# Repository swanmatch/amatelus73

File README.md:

# Amatelus73ビルドガイド

## 概要

m.teiさんの[セミエルゴレイアウト](https://github.com/mtei/SemiErgo_Layout)を参考に作成したシンメトリカルスタッガードキーボード。  
RGBMATRIXに標準対応しているのも特徴。

### 材料リスト

| 品目                    | 数量 | 備考 |
| :---------------------- | ---: | :--- |
| PCB                     |  1枚 |  |
| トッププレート          |  1枚 |  |
| ボトムプレート          |  1枚 |  |
| アクリル保護プレート    |  2枚 |  |
| ProMicro                |  1個 |  |
| ダイオード              | 73個 | スピーカーを使う場合74個。<br>スルーホールは使えないので注意。 |
| LED(YS-SK6812mini)      | 74個 |  |
| Kailhソケット           | 73個 |  |
| M2L4ネジ                | 18本 |  |
| M2L7六角スペーサ        |  5本 |  |
| M2L8丸スペーサ          |  4本 |  |
| タクトスイッチ          |  1個 |  |
| ゴム足                  |  4個 |  |
| 2Uスタビライザー         |  4個 |  |
| MX互換スイッチ          | 73個 |  |
| キーキャップ            | 73個 |  |
| USBケーブル             |  1本 |  |

### オプション機能

| 品目             | 数量 | 備考 |
| :--------------- | ---: | :--- |
| コンスルー       |  2本 |  |
| 圧電サウンダ     |  1個 | スピーカーオプション<br>型番: PKMCS1212E4000-R1 |
| 1kΩ抵抗         |  1個 | スピーカーオプション |
| OLED             |  1個 | ピン、ソケットも。 |

## 組み立て手順

### LED

LEDをはんだ付けします。  
小さくドットが入っているのが欠けている足に対応しています。

行ごと向きが違うので注意してください。

### ダイオード

ダイオードをはんだ付けします。  
向きに気をつけてください。  
うっすら線が書いてあるほうが左です。

先に予備ハンダとしてどちらかのパッドにハンダを盛って、
予備ハンダを溶かすようにしてダイオードの片足をはんだ付けします。  
この状態で横から見てダイオードが浮いていないことを確認してください。  
浮いてしまっている場合はダイオードをピンセットで押さえつけながら、
はんだづけした部分を再度熱すればきれいになります。

浮いていないことを確認し、反対側をはんだ付けします。

### ソケット

ソケットをはんだ付けします。

### リセットスイッチ

反対側(表、スイッチ側)にひっくり返して、
タクトスイッチを差し込み、
再度裏面に戻してはんだ付けします。

### 圧電サウンダ(オプション)

1kΩ抵抗、ダイオード、圧電サウンダをはんだ付けします。

### ProMicro

ここだけは間違えるとリカバリが面倒なので、**細心の注意**をして作業にあたってください  
コンスルーを使う場合は[Helixのビルドガイド](https://github.com/MakotoKurauchi/helix/blob/master/Doc/buildguide_jp.md#pro-micro)などを参考にしてください。  
また、ProMicroはあらかじめいわゆる「モゲ対策」をしておくといいです。

まず4角のピンをはんだ付けし、
ピンヘッダとプロマイクロが浮いていないことを確認して、
他のピンをはんだ付けします。  
浮いてしまっていた場合、やけどに気を付けて、指で少し抑えながら、
浮いているピンにハンダをあてます。
裏面に戻し、表面と同様に4角からはんだ付けしていきます。

この段階で一度後述のLEDテスト用のファームウェアの書き込みをして導通テストしておくといいです。  
問題なければ全LEDが点灯するはずです。  
(RGB_MATRIXはキー押下に応じてLEDが光るモードがデフォルトになっているようなのでLED_testで確認するのが吉です。)

```sh
git clone https://github.com/swanmatch/qmk_firmware.git --recursive
cd qmk_firmware
make amatelus73:led_test:avrdude
```

### OLED(オプション)

OLEDにピンをはんだ付けし、基板側にソケットをはんだ付けします。
いずれも斜めになりやすいので注意してください。

### スタビライザ

スタビライザを組み立てて、回路基板にはめ込みます。

### スイッチ、トッププレート

トッププレートにスイッチをはめて、PCBに刺します。  
これも最初に4角からはめるといいです。

### プロマイクロ保護プレート

PCB裏側から丸スペーサーをネジ止めして、
表側に保護プレートを挟み込む形でPCネジで止めます。

### ボトムプレート

ボトムプレートに六角スペーサーをネジ止めして、
本体にはめ込み、ネジ止めします。

ボトムプレートにゴム足を貼り付けてください。

### ファームウェア

ファームウェアの書き込みは以下のコマンドを叩きます。  
QMKの環境構築についてはお使いのOSによって異なりなりますので、
公式ドキュメントを読んでください。
```sh
# LEDテストの書き込みを実施した場合は↓は不要
git clone https://github.com/swanmatch/qmk_firmware.git --recursive
cd qmk_firmware
make amatelus73:default:avrdude
# OLED ver
# amatelus73/oled:default:avrdude
# Audio ver
# amatelus73/audio:default:avrdude
```

### キーキャップ

キーキャップの取り付けは下記を推奨しています。  
図はm.teiさんに作成いただきました。

Special Thanks!!

## 完成図

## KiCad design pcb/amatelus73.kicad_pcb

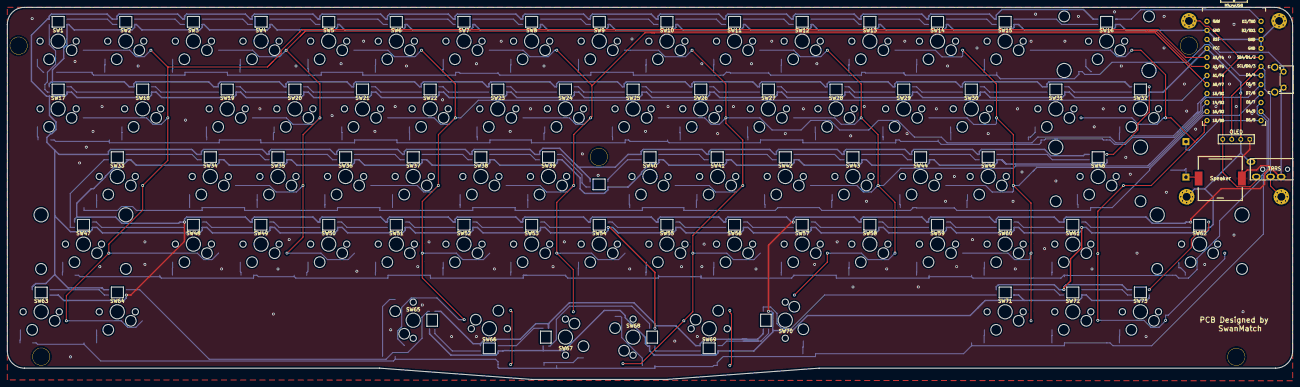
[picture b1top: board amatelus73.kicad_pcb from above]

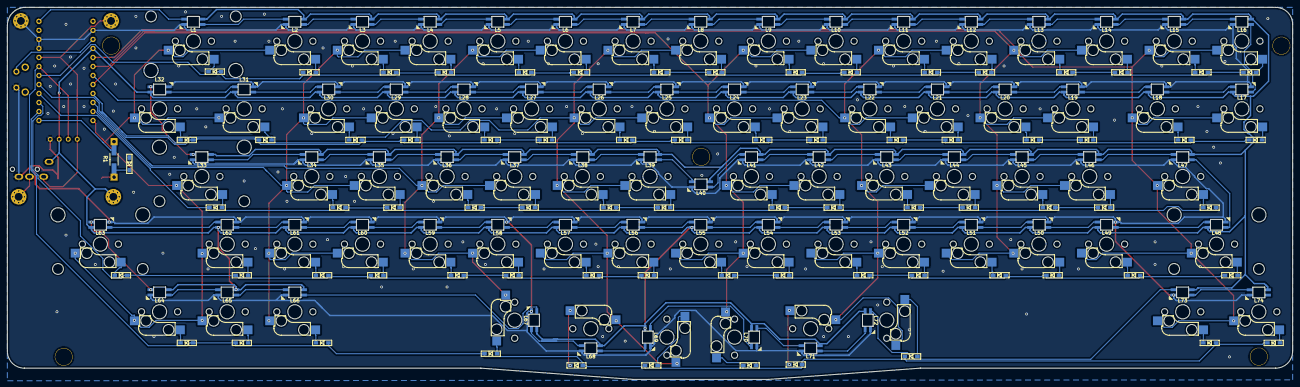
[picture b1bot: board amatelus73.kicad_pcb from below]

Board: 2 copper layers, 361.9 x 104.8 mm, 236 parts (149 on the bottom side), 167 nets.

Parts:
D1, D2, D3, D4, D5, D6, D7, D8, D9, D10, D11, D12, D13, D14, D15, D16, D17, D18, D19, D20, D21, D22, D23, D24, D25, D26, D27, D28, D29, D30, D31, D32, D33, D34, D35, D36, D37, D38, D39, D40, D41, D42, D43, D44, D45, D46, D47, D48, D49, D50, D51, D52, D53, D54, D55, D56, D57, D58, D59, D60, D61, D62, D63, D64, D65, D66, D67, D68, D69, D70, D71, D72, D73, D74: D; D3_SMD
Hole1, Hole2, Hole3, Hole4, Hole5: Val**; HOLE
J1: Conn_01x04; OLED_1side
J2: AudioJack4; MJ-4PP-9_1side
L1, L2, L3, L4, L5, L6, L7, L8, L9, L10, L11, L12, L13, L14, L15, L16, L17, L18, L19, L20, L21, L22, L23, L24, L25, L26, L27, L28, L29, L30, L31, L32, L33, L34, L35, L36, L37, L38, L39, L40, L41, L42, L43, L44, L45, L46, L47, L48, L49, L50, L51, L52, L53, L54, L55, L56, L57, L58, L59, L60, L61, L62, L63, L64, L65, L66, L67, L68, L69, L70, L71, L72, L73, L74: YS-SK6812MINI; YS-SK6812MINI-E
R1: R; Resistor_SMD+THTuniversal_1206_RM10_HandSoldering
SC1, SC2, SC3, SC4: MountingHole_2.2mm_M2_Pad_Via
SW1, SW2, SW3, SW4, SW5, SW6, SW7, SW8, SW9, SW10, SW11, SW12, SW13, SW14, SW15, SW17, SW19, SW20, SW21, SW22, SW23, SW24, SW25, SW26, SW27, SW28, SW29, SW30, SW32, SW34, SW35, SW36, SW37, SW38, SW39, SW40, SW41, SW42, SW43, SW44, SW45, SW48, SW49, SW50, SW51, SW52, SW53, SW54, SW55, SW56, SW57, SW58, SW59, SW60, SW61, SW63, SW71, SW72, SW73: SW_PUSH; MX_Hotswap_1u
SW16: SW_PUSH; MX_Hotswap_2u_Reversed
SW18, SW31: SW_PUSH; MX_Hotswap_1.5u
SW33: SW_PUSH; MX_Hotswap_1.75u
SW46, SW47: SW_PUSH; MX_Hotswap_2.25u
SW62: SW_PUSH; MX_Hotswap_2.75u
SW64, SW65, SW66, SW67, SW68, SW69, SW70: SW_PUSH; MX_Hotswap_1.25u
SW74: SW_PUSH; SW_Tactile_SPST_Angled_PTS645Vx31-2LFS
Speaker: Speaker; PKLCS1212E4001_HandSoldering
U1: ProMicro_r; ProMicro_v3

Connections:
AUDIO: R1.2, U1.12
COL1: SW1.1, SW2.1, SW17.1, SW18.1, SW33.1, SW47.1, SW48.1, SW63.1, SW64.1, U1.20
COL2: SW3.1, SW4.1, SW19.1, SW20.1, SW34.1, SW35.1, SW49.1, SW50.1, U1.19
COL3: SW5.1, SW6.1, SW21.1, SW22.1, SW36.1, SW37.1, SW51.1, SW52.1, SW65.1, SW66.1, U1.18
COL4: SW7.1, SW8.1, SW23.1, SW24.1, SW38.1, SW39.1, SW53.1, SW54.1, SW67.1, U1.17
COL5: SW9.1, SW10.1, SW25.1, SW26.1, SW40.1, SW41.1, SW55.1, SW56.1, SW68.1, SW69.1, U1.16
COL6: SW11.1, SW12.1, SW27.1, SW28.1, SW42.1, SW43.1, SW57.1, SW58.1, SW70.1, U1.15
COL7: SW13.1, SW14.1, SW29.1, SW30.1, SW44.1, SW45.1, SW59.1, SW60.1, SW71.1, U1.14
COL8: SW15.1, SW16.1, SW31.1, SW32.1, SW46.1, SW61.1, SW62.1, SW72.1, SW73.1, U1.13
GND: D74.2, J1.4, J2.S, L1.3, L2.3, L3.3, L4.3, L5.3, L6.3, L7.3, L8.3, L9.3, L10.3, L11.3, L12.3, L13.3, L14.3, L15.3, L16.3, L17.3, L18.3, L19.3, L20.3, L21.3, L22.3, L23.3, L24.3, L25.3, L26.3, L27.3, L28.3, L29.3, L30.3, L31.3, L32.3, L33.3, L34.3, L35.3, L36.3, L37.3, L38.3, L39.3, L40.3, L41.3, L42.3, L43.3, L44.3, L45.3, L46.3, L47.3, L48.3, L49.3, L50.3, L51.3, L52.3, L53.3, L54.3, L55.3, L56.3, L57.3, L58.3, L59.3, L60.3, L61.3, L62.3, L63.3, L64.3, L65.3, L66.3, L67.3, L68.3, L69.3, L70.3, L71.3, L72.3, L73.3, L74.3, SC2.1, SW74.2, Speaker.2, U1.3, U1.4, U1.23
LED: L1.4, U1.1
unnamed: D1.2, SW1.2
unnamed: D2.1, SW2.2
unnamed: D3.2, SW3.2
unnamed: D4.1, SW4.2
unnamed: D5.2, SW5.2
unnamed: D6.1, SW6.2
unnamed: D7.2, SW7.2
unnamed: D8.1, SW8.2
unnamed: D9.2, SW9.2
unnamed: D10.1, SW10.2
unnamed: D11.2, SW11.2
unnamed: D12.1, SW12.2
unnamed: D13.2, SW13.2
unnamed: D14.1, SW14.2
unnamed: D15.2, SW15.2
unnamed: D16.1, SW16.2
unnamed: D17.2, SW17.2
unnamed: D18.1, SW18.2
unnamed: D19.2, SW19.2
unnamed: D20.1, SW20.2
unnamed: D21.2, SW21.2
unnamed: D22.1, SW22.2
unnamed: D23.2, SW23.2
unnamed: D24.1, SW24.2
unnamed: D25.2, SW25.2
unnamed: D26.1, SW26.2
unnamed: D27.2, SW27.2
unnamed: D28.1, SW28.2
unnamed: D29.2, SW29.2
unnamed: D30.1, SW30.2
unnamed: D31.2, SW31.2
unnamed: D32.1, SW32.2
unnamed: D33.1, SW33.2
unnamed: D34.2, SW34.2
unnamed: D35.1, SW35.2
unnamed: D36.2, SW36.2
unnamed: D37.1, SW37.2
unnamed: D38.2, SW38.2
unnamed: D39.1, SW39.2
unnamed: D40.2, SW40.2
unnamed: D41.1, SW41.2
unnamed: D42.2, SW42.2
unnamed: D43.1, SW43.2
unnamed: D44.2, SW44.2
unnamed: D45.1, SW45.2
unnamed: D46.2, SW46.2
unnamed: D47.2, SW47.2
unnamed: D48.1, SW48.2
unnamed: D49.2, SW49.2
unnamed: D50.1, SW50.2
unnamed: D51.2, SW51.2
unnamed: D52.1, SW52.2
unnamed: D53.2, SW53.2
unnamed: D54.1, SW54.2
unnamed: D55.2, SW55.2
unnamed: D56.1, SW56.2
unnamed: D57.2, SW57.2
unnamed: D58.1, SW58.2
unnamed: D59.2, SW59.2
unnamed: D60.1, SW60.2
unnamed: D61.2, SW61.2
unnamed: D62.1, SW62.2
unnamed: D63.2, SW63.2
unnamed: D64.1, SW64.2
unnamed: D65.2, SW65.2
unnamed: D66.1, SW66.2
unnamed: D67.2, SW67.2
unnamed: D68.2, SW68.2
unnamed: D69.1, SW69.2
unnamed: D70.2, SW70.2
unnamed: D71.1, SW71.2
unnamed: D72.2, SW72.2
unnamed: D73.1, SW73.2
unnamed: D74.1, R1.1, Speaker.1
unnamed: L1.2, L2.4
unnamed: L2.2, L3.4
unnamed: L3.2, L4.4
unnamed: L4.2, L5.4
unnamed: L5.2, L6.4
unnamed: L6.2, L7.4
unnamed: L7.2, L8.4
unnamed: L8.2, L9.4
unnamed: L10.2, L11.4
unnamed: L9.2, L10.4
unnamed: L11.2, L12.4
unnamed: L12.2, L13.4
unnamed: L13.2, L14.4
unnamed: L14.2, L15.4
unnamed: L15.2, L16.4
unnamed: L16.2, L17.4
unnamed: L17.2, L18.4
unnamed: L18.2, L19.4
unnamed: L19.2, L20.4
unnamed: L20.2, L21.4
unnamed: L21.2, L22.4
unnamed: L22.2, L23.4
unnamed: L23.2, L24.4
unnamed: L24.2, L25.4
unnamed: L25.2, L26.4
unnamed: L26.2, L27.4
unnamed: L27.2, L28.4
unnamed: L28.2, L29.4
unnamed: L29.2, L30.4
unnamed: L30.2, L31.4
unnamed: L31.2, L32.4
unnamed: L32.2, L33.4
unnamed: L33.2, L34.4
unnamed: L34.2, L35.4
unnamed: L35.2, L36.4
unnamed: L36.2, L37.4
unnamed: L37.2, L38.4
unnamed: L38.2, L39.4
unnamed: L39.2, L40.4
unnamed: L40.2, L41.4
unnamed: L41.2, L42.4
unnamed: L42.2, L43.4
unnamed: L43.2, L44.4
unnamed: L44.2, L45.4
unnamed: L45.2, L46.4
unnamed: L46.2, L47.4
unnamed: L47.2, L48.4
unnamed: L48.2, L49.4
unnamed: L49.2, L50.4
unnamed: L50.2, L51.4
unnamed: L51.2, L52.4
unnamed: L52.2, L53.4
unnamed: L53.2, L54.4
unnamed: L54.2, L55.4
unnamed: L55.2, L56.4
unnamed: L56.2, L57.4
unnamed: L57.2, L58.4
unnamed: L58.2, L59.4
unnamed: L59.2, L60.4
unnamed: L60.2, L61.4
unnamed: L61.2, L62.4
unnamed: L62.2, L63.4
unnamed: L63.2, L64.4
unnamed: L64.2, L65.4
unnamed: L65.2, L66.4
unnamed: L66.2, L67.4
unnamed: L67.2, L68.4
unnamed: L68.2, L69.4
unnamed: L69.2, L70.4
unnamed: L70.2, L71.4
unnamed: L71.2, L72.4
unnamed: L72.2, L73.4
unnamed: L73.2, L74.4
ROW1: D1.1, D2.2, D3.1, D4.2, D5.1, D6.2, D7.1, D8.2, D9.1, D10.2, D11.1, D12.2, D13.1, D14.2, D15.1, D16.2, U1.7
ROW2: D17.1, D18.2, D19.1, D20.2, D21.1, D22.2, D23.1, D24.2, D25.1, D26.2, D27.1, D28.2, D29.1, D30.2, D31.1, D32.2, U1.8
ROW3: D33.2, D34.1, D35.2, D36.1, D37.2, D38.1, D39.2, D40.1, D41.2, D42.1, D43.2, D44.1, D45.2, D46.1, U1.9
ROW4: D47.1, D48.2, D49.1, D50.2, D51.1, D52.2, D53.1, D54.2, D55.1, D56.2, D57.1, D58.2, D59.1, D60.2, D61.1, D62.2, U1.10
ROW5: D63.1, D64.2, D65.1, D66.2, D67.1, D68.1, D69.2, D70.1, D71.2, D72.1, D73.2, U1.11
RST: SW74.1, U1.22
SCL: J1.2, J2.R2, SC4.1, U1.6
SDA: J1.1, J2.R1, SC1.1, U1.5
VCC: J1.3, J2.T, L1.1, L2.1, L3.1, L4.1, L5.1, L6.1, L7.1, L8.1, L9.1, L10.1, L11.1, L12.1, L13.1, L14.1, L15.1, L16.1, L17.1, L18.1, L19.1, L20.1, L21.1, L22.1, L23.1, L24.1, L25.1, L26.1, L27.1, L28.1, L29.1, L30.1, L31.1, L32.1, L33.1, L34.1, L35.1, L36.1, L37.1, L38.1, L39.1, L40.1, L41.1, L42.1, L43.1, L44.1, L45.1, L46.1, L47.1, L48.1, L49.1, L50.1, L51.1, L52.1, L53.1, L54.1, L55.1, L56.1, L57.1, L58.1, L59.1, L60.1, L61.1, L62.1, L63.1, L64.1, L65.1, L66.1, L67.1, L68.1, L69.1, L70.1, L71.1, L72.1, L73.1, L74.1, SC3.1, U1.21

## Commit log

2020-02-18 first order
2020-06-14 2nd order
2020-07-24 add readme
2020-07-26 Set theme jekyll-theme-cayman
2020-08-29 thanks m.tei.
2021-01-12 fix silk
2021-01-21 fix build order
2021-01-21 add stab image
